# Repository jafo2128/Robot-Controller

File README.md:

# Robot-Controller
Robot-Controller Shield for Wattuino Pro Mini.

## Shop
* [Robot-Controller Shield](http://www.watterott.com/en/Robot-Controller)
* [Robot-Controller Shield with Wattuino Pro Mini](http://www.watterott.com/en/Robot-Controller-with-Wattuino-Pro-Mini-5V/16MHz)

## Features
* [TI DRV8838](http://www.ti.com/product/drv8838) Motor Driver (2-11V 1.8A)
* [FTDI FT232R](http://www.ftdichip.com/Products/ICs/FT232R.htm) USB-UART Bridge (microUSB)
* Power MOSFET
* Extension Ports for Servo Motor or Sensors

## Hardware
* [Schematics + Layout](https://github.com/watterott/Robot-Controller/tree/master/hardware)

Finally words from us Archivers and Developers.. 

##### Donate

People from time to time wish to donate a little money. Donating won't get you anything special, other than a warm feeling inside, and possibly urge me to produce more freely available material for interesting projects. You can donate via [PayPal](https://www.paypal.com), just click [donate](https://www.paypal.com/cgi-bin/webscr?cmd=_s-xclick&hosted_button_id=3PXVSLXFBS45E) button available below - it will redirect you to the secured PayPal page where you can provide donation amount (there is no minimal value). Any donations are apreciated greatly, and we thank you all in advance for your support along the ways..

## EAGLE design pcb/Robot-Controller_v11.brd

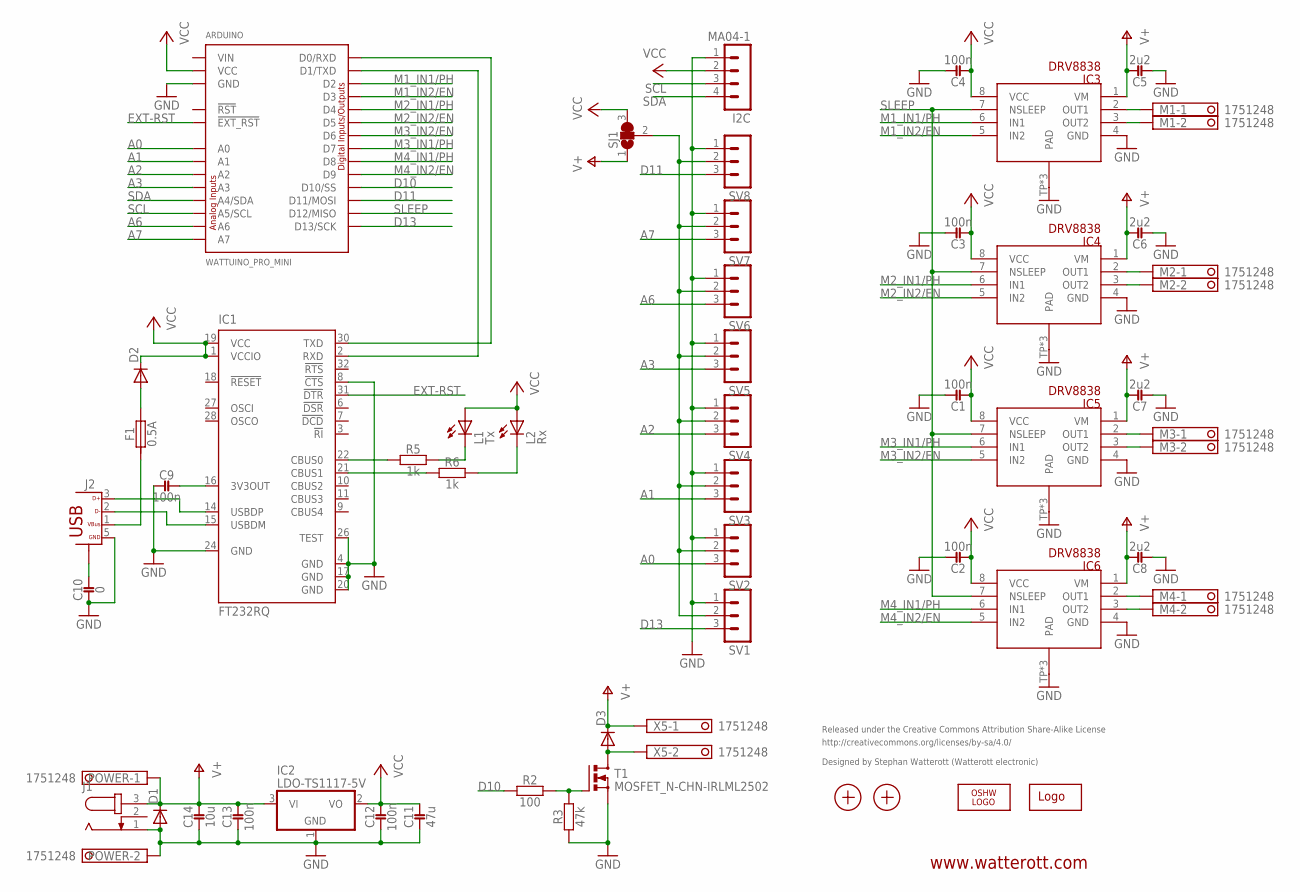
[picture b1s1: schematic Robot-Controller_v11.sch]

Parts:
ARDUINO: WATTUINO_PRO_MINI
C1, C2, C3, C4, C9, C12, C13: 100n; R0603
C5, C6, C7, C8: 2u2; R0603
C10: 0; R0603
C11: 47u; R1206
C14: 10u; R1206
D1, D2, D3: CGRM4001-G; SOD-123_MINI-SMA
F1: 0.5A; R0805
I2C: MA04-1
IC1: FT232RQ; QFN32
IC2: LDO-TS1117-5V; SOT223
IC3, IC4, IC5, IC6: DRV8838; WSON8
J1: DC-JACK""; DC-JACK
J2: USB10103594-0001LF; 10103594
L1: Tx; LED_0603
L2: Rx; LED_0603
LOGO2: OSHW_LOGOX0100; OSHW_6X100
LOGO3: LOGO-SPARK_PLACE; SPARK_TPLACE
M1, M2, M3, M4: 1751248
POWER: 1751248
R2: 100; R0603
R3: 47k; R0603
R5, R6: 1k; R0603
SJ1: SJ2W; SJ_2
SV1, SV2, SV3, SV4, SV5, SV6, SV7, SV8: MA03-1
T1: MOSFET_N-CHN-IRLML2502; SOT23
X1, X2: PASSER-07; PASSER_07MM
X5: 1751248

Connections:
A0: ARDUINO.A0, SV2.3
A1: ARDUINO.A1, SV3.3
A2: ARDUINO.A2, SV4.3
A3: ARDUINO.A3, SV5.3
A6: ARDUINO.A6, SV6.3
A7: ARDUINO.A7, SV7.3
D10: ARDUINO.10 (D10/SS), R2.1
D11: ARDUINO.11 (D11/MOSI), SV8.3
D13: ARDUINO.13 (D13/SCK), SV1.3
EXT-RST: ARDUINO.EXT_RST (!EXT_RST), IC1.31 (!DTR)
GND: ARDUINO.GND@1 (GND), C1.2, C2.2, C3.2, C4.2, C5.1, C6.1, C7.1, C8.1, C9.1, C10.1, C11.1, C12.1, C13.1, C14.1, D1.A, I2C.1, IC1.4 (GND), IC1.8 (!CTS), IC1.17 (GND), IC1.20 (GND), IC1.24 (GND), IC1.26 (TEST), IC2.1 (GND), IC3.4 (GND), IC3.TP (PAD), IC3.TP1 (PAD), IC3.TP2 (PAD), IC4.4 (GND), IC4.TP (PAD), IC4.TP1 (PAD), IC4.TP2 (PAD), IC5.4 (GND), IC5.TP (PAD), IC5.TP1 (PAD), IC5.TP2 (PAD), IC6.4 (GND), IC6.TP (PAD), IC6.TP1 (PAD), IC6.TP2 (PAD), J1.1, J2.5 (GND), POWER.2, R3.1, SV1.1, SV2.1, SV3.1, SV4.1, SV5.1, SV6.1, SV7.1, SV8.1, T1.2 (S)
M1_IN1/PH: ARDUINO.2 (D2), IC3.6 (IN1)
M1_IN2/EN: ARDUINO.3 (D3), IC3.5 (IN2)
M2_IN1/PH: ARDUINO.4 (D4), IC4.6 (IN1)
M2_IN2/EN: ARDUINO.5 (D5), IC4.5 (IN2)
M3_IN1/PH: ARDUINO.7 (D7), IC5.6 (IN1)
M3_IN2/EN: ARDUINO.6 (D6), IC5.5 (IN2)
M4_IN1/PH: ARDUINO.8 (D8), IC6.6 (IN1)
M4_IN2/EN: ARDUINO.9 (D9), IC6.5 (IN2)
unnamed: IC3.2 (OUT1), M1.1
unnamed: IC3.3 (OUT2), M1.2
unnamed: IC4.2 (OUT1), M2.1
unnamed: IC4.3 (OUT2), M2.2
unnamed: IC5.2 (OUT1), M3.1
unnamed: IC5.3 (OUT2), M3.2
unnamed: IC6.2 (OUT1), M4.1
unnamed: IC6.3 (OUT2), M4.2
unnamed: F1.1, J2.1 (VBUS)
unnamed: IC1.15 (USBDM), J2.2 (D-)
unnamed: R2.2, R3.2, T1.1 (G)
unnamed: C9.2, IC1.16 (3V3OUT)
unnamed: ARDUINO.RXD@1 (D0/RXD), IC1.30 (TXD)
unnamed: D3.A, T1.3 (D), X5.2
unnamed: IC1.14 (USBDP), J2.3 (D+)
unnamed: ARDUINO.TXD@1 (D1/TXD), IC1.2 (RXD)
unnamed: IC1.22 (CBUS0), R5.1
unnamed: IC1.21 (CBUS1), R6.1
unnamed: SJ1.2, SV1.2, SV2.2, SV3.2, SV4.2, SV5.2, SV6.2, SV7.2, SV8.2
unnamed: C10.2, J2.P$6 (SHIELD), J2.P$7 (SHIELD)
unnamed: D2.A, F1.2
unnamed: L1.C, R5.2
unnamed: L2.C, R6.2
SCL: ARDUINO.A5 (A5/SCL), I2C.3
SDA: ARDUINO.A4 (A4/SDA), I2C.4
SLEEP: ARDUINO.12 (D12/MISO), IC3.7 (NSLEEP), IC4.7 (NSLEEP), IC5.7 (NSLEEP), IC6.7 (NSLEEP)
V+: C5.2, C6.2, C7.2, C8.2, C13.2, C14.2, D1.C, D3.C, IC2.3 (VI), IC3.1 (VM), IC4.1 (VM), IC5.1 (VM), IC6.1 (VM), J1.3, POWER.1, SJ1.1, X5.1
VCC: ARDUINO.VCC@1 (VCC), C1.1, C2.1, C3.1, C4.1, C11.2, C12.2, D2.C, I2C.2, IC1.1 (VCCIO), IC1.19 (VCC), IC2.2 (VO), IC3.8 (VCC), IC4.8 (VCC), IC5.8 (VCC), IC6.8 (VCC), L1.A, L2.A, SJ1.3
VIN: ARDUINO.VIN

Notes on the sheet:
www.watterott.com
Released under the Creative Commons Attribution Share-Alike License
http://creativecommons.org/licenses/by-sa/4.0/
Designed by Stephan Watterott (Watterott electronic)

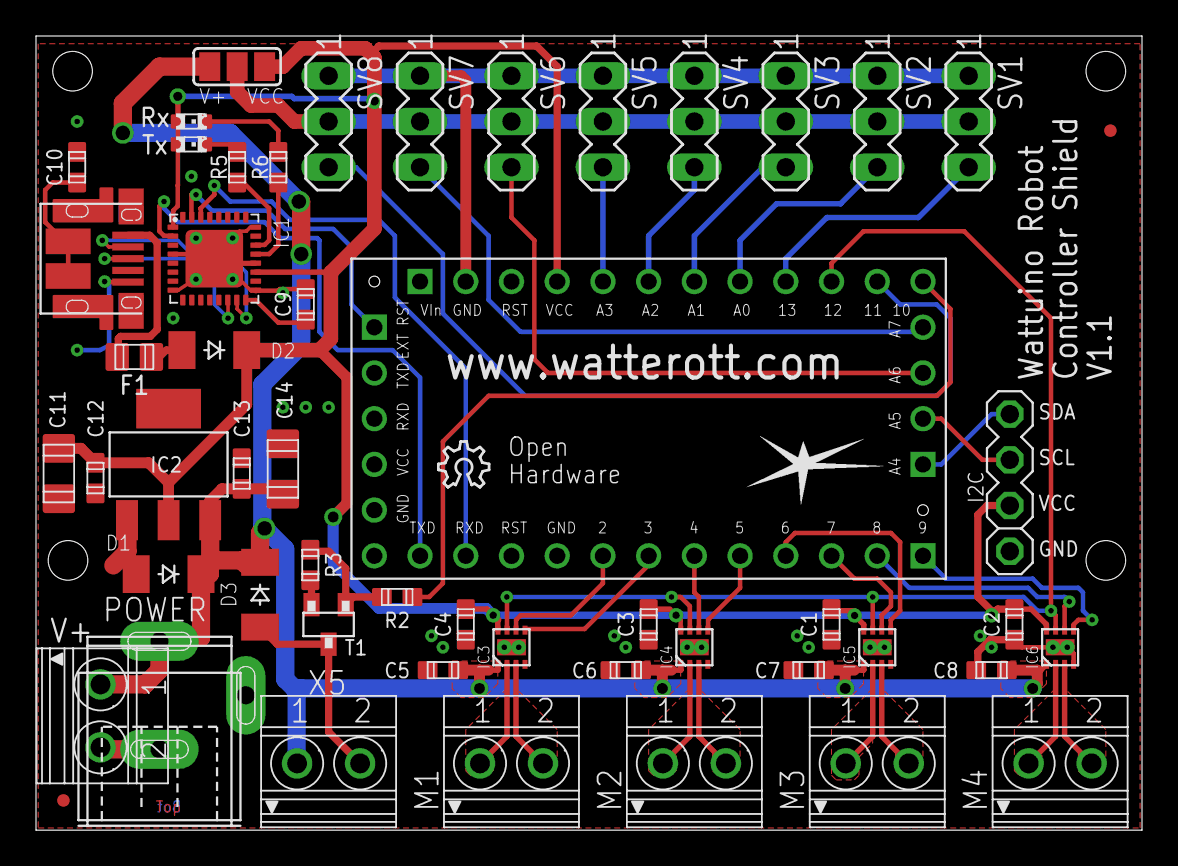
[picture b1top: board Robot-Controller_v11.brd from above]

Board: 2 copper layers, 61.4 x 44.1 mm, 54 parts (0 on the bottom side), 47 nets.

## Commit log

2014-08-21 added readme
2014-08-23 added layout and schematics
2014-08-25 added image
2014-08-29 updated layout and schematics
2014-11-06 cleaned up schematics and layout
2015-01-11 moved image
2015-08-21 changed path structure

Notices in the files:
parts and their libraries:
wattuino: This work is licensed under a Creative Commons Attribution-ShareAlike 3.0 Unported License.
